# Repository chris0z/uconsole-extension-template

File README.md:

Licence | OSHWA
:-------------------------:|:-------------------------:
 | 
CERN-OHL-S-2.0

# uConsole Ext Template

This extension board is a basic Template for [uConsole](https://www.clockworkpi.com/uconsole).
Thanks to https://codeberg.org/argrento/uconsole-ext-usb-hub
## Schematic

## PCB

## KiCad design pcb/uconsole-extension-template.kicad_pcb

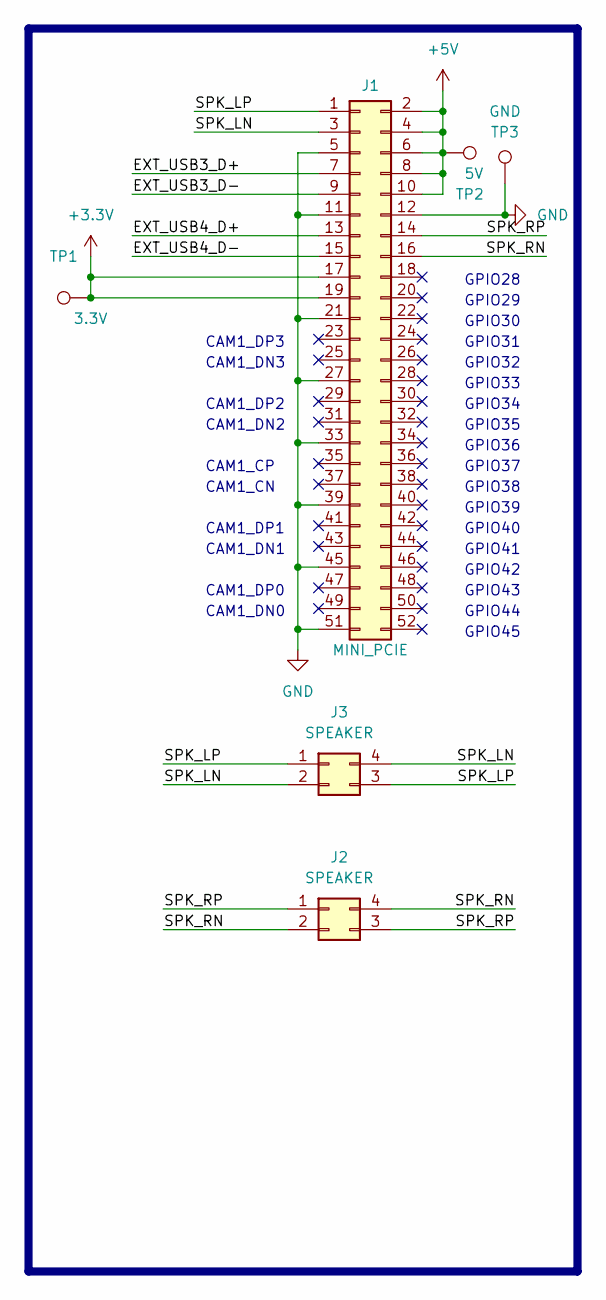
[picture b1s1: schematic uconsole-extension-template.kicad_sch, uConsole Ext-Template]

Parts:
J1: MINI_PCIE; mini_pcie_edge
J2, J3: SPEAKER; uConsole_speaker
TP1: 3.3V; PinHeader_1x01_P2.54mm_Vertical
TP2: 5V; PinHeader_1x01_P2.54mm_Vertical
TP3: GND; PinHeader_1x01_P2.54mm_Vertical

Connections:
+3.3V: J1.17, J1.19, TP1.1
+5V: J1.2, J1.4, J1.6, J1.8, J1.10, TP2.1
/EXT_USB3_D+: J1.7
/EXT_USB3_D-: J1.9
/EXT_USB4_D+: J1.13
/EXT_USB4_D-: J1.15
/SPK_LN: J1.3, J3.2, J3.4
/SPK_LP: J1.1, J3.1, J3.3
/SPK_RN: J1.16, J2.2, J2.4
/SPK_RP: J1.14, J2.1, J2.3
GND: J1.5, J1.11, J1.12, J1.21, J1.27, J1.33, J1.39, J1.45, J1.51, TP3.1

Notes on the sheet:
CAM1_DN1
GPIO43
CAM1_DP3
CAM1_DP0
GPIO31
GPIO42
CAM1_DN3
GPIO29
CAM1_DP2
GPIO41
CAM1_DP1
GPIO32
GPIO28
GPIO38
GPIO30
CAM1_DN2
CAM1_DN0
GPIO39
CAM1_CP
GPIO34
GPIO37
GPIO33
CAM1_CN
GPIO36
GPIO35
GPIO44
GPIO45
GPIO40

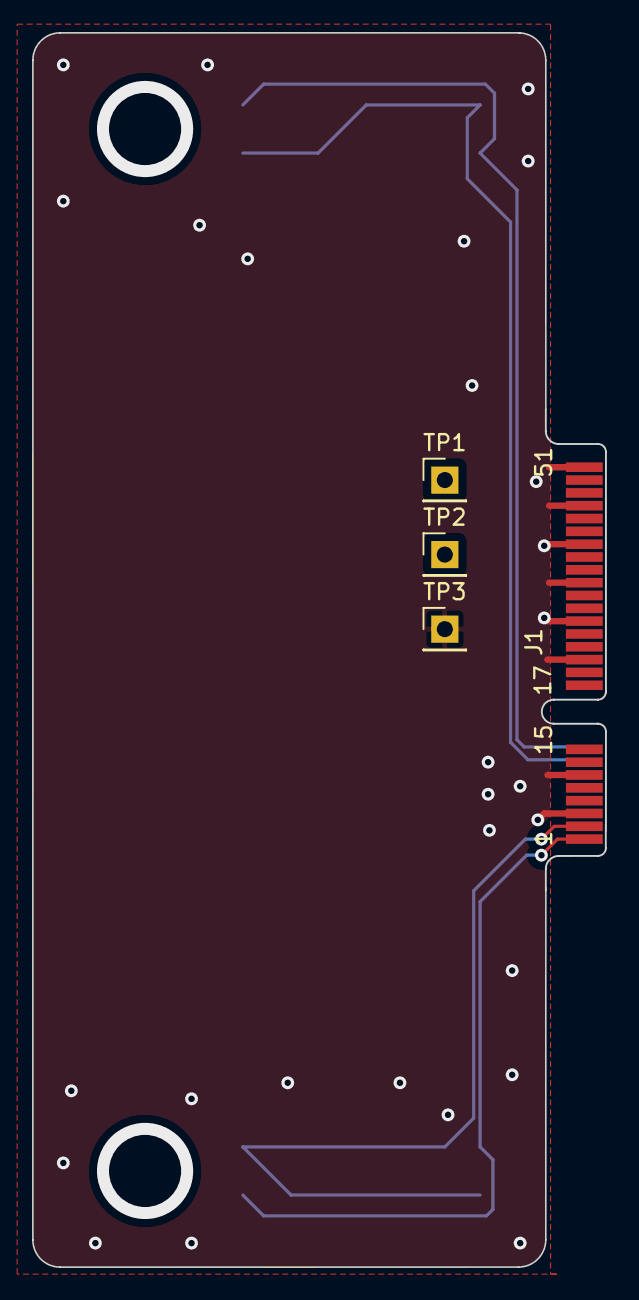
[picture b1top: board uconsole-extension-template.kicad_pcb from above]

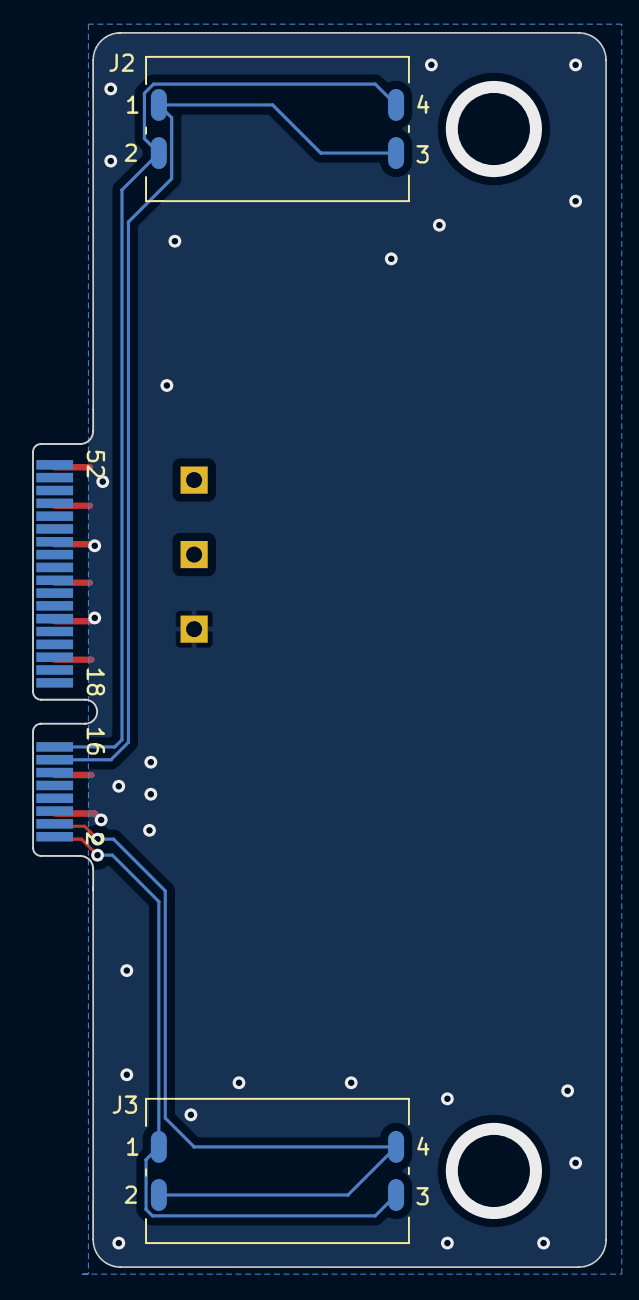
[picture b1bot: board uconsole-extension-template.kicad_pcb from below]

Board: 2 copper layers, 35.7 x 77.0 mm, 6 parts (2 on the bottom side), 7 nets.

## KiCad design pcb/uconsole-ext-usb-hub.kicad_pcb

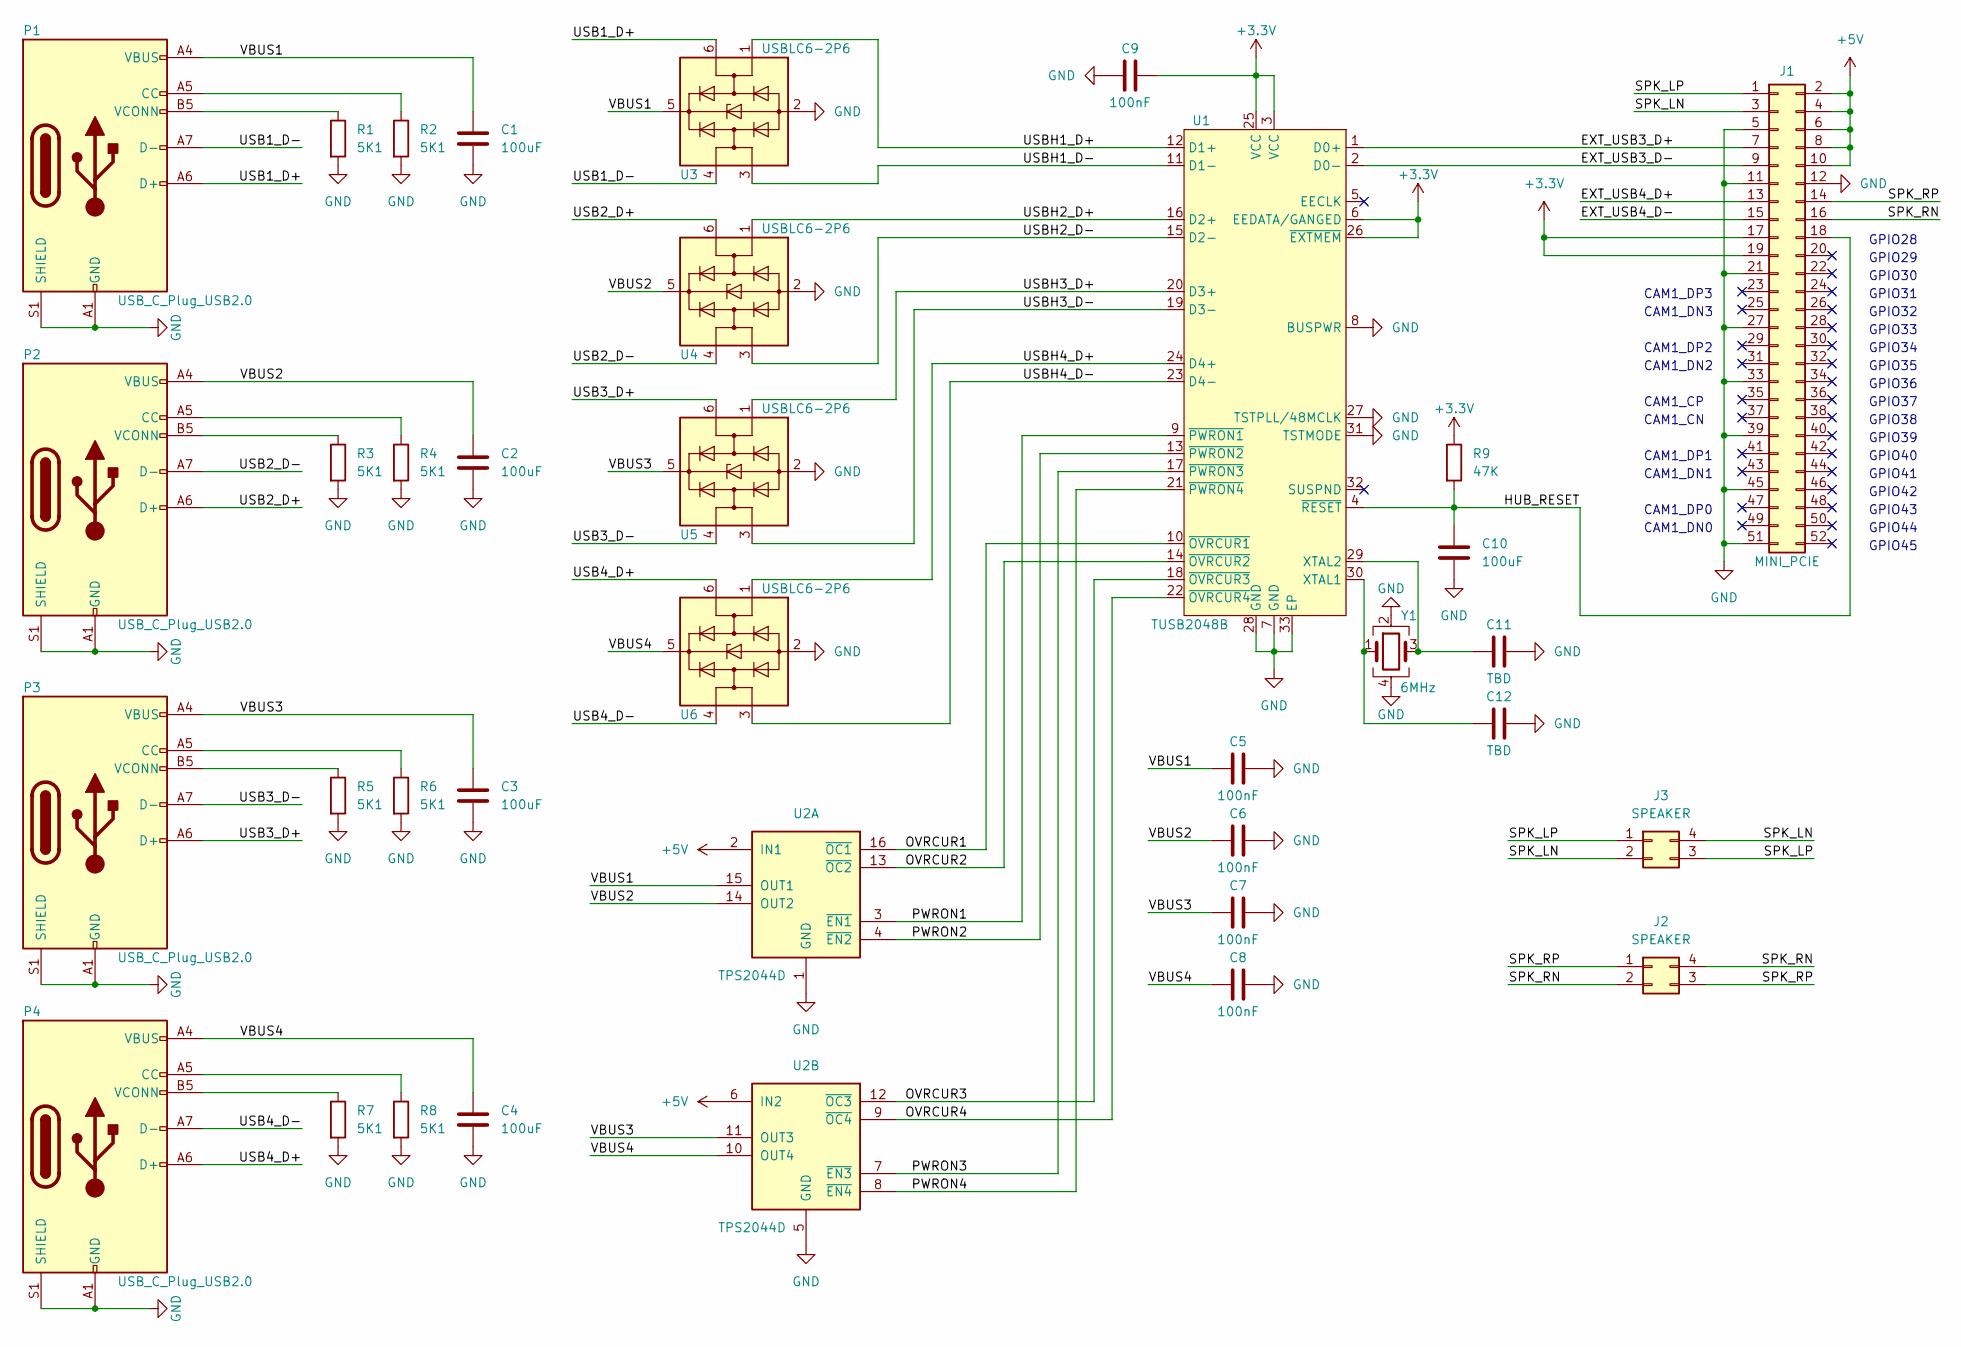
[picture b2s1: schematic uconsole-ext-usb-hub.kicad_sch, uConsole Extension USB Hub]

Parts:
C1, C2, C3, C4, C10: 100uF; C_0805_2012Metric
C5, C6, C7, C8, C9: 100nF; C_0603_1608Metric
C11, C12: TBD; C_0603_1608Metric
J1: MINI_PCIE; mini_pcie_edge
J2, J3: SPEAKER; uConsole_speaker
P1, P2, P3, P4: USB_C_Plug_USB2.0; USB_C_Receptacle_GCT_USB4105-xx-A_16P_TopMnt_Horizontal
R1, R2, R3, R4, R5, R6, R7, R8: 5K1; R_0603_1608Metric
R9: 47K; R_0603_1608Metric
U1: TUSB2048B; QFN-32-1EP_5x5mm_P0.5mm_EP3.3x3.3mm_ThermalVias
U2: TPS2044D; SOIC-16_3.9x9.9mm_P1.27mm
U3, U4, U5, U6: USBLC6-2P6; SOT-666
Y1: 6MHz; Crystal_SMD_2016-4Pin_2.0x1.6mm

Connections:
+3.3V: C9.1, J1.17, J1.19, R9.1, U1.3 (VCC), U1.6 (EEDATA/GANGED), U1.25 (VCC), U1.26 (~EXTMEM)
+5V: J1.2, J1.4, J1.6, J1.8, J1.10, U2.2 (IN1), U2.6 (IN2)
/EXT_USB3_D+: J1.7, U1.1 (D0+)
/EXT_USB3_D-: J1.9, U1.2 (D0-)
/EXT_USB4_D+: J1.13
/EXT_USB4_D-: J1.15
/HUB_RESET: C10.1, J1.18, R9.2, U1.4 (~RESET)
/OVRCUR1: U1.10 (~OVRCUR1), U2.16 (~OC1)
/OVRCUR2: U1.14 (~OVRCUR2), U2.13 (~OC2)
/OVRCUR3: U1.18 (~OVRCUR3), U2.12 (~OC3)
/OVRCUR4: U1.22 (~OVRCUR4), U2.9 (~OC4)
/PWRON1: U1.9 (~PWRON1), U2.3 (~EN1)
/PWRON2: U1.13 (~PWRON2), U2.4 (~EN2)
/PWRON3: U1.17 (~PWRON3), U2.7 (~EN3)
/PWRON4: U1.21 (~PWRON4), U2.8 (~EN4)
/SPK_LN: J1.3, J3.2, J3.4
/SPK_LP: J1.1, J3.1, J3.3
/SPK_RN: J1.16, J2.2, J2.4
/SPK_RP: J1.14, J2.1, J2.3
/USB1_D+: P1.A6 (D+), U3.6 (I/O1)
/USB1_D-: P1.A7 (D-), U3.4 (I/O2)
/USB2_D+: P2.A6 (D+), U4.6 (I/O1)
/USB2_D-: P2.A7 (D-), U4.4 (I/O2)
/USB3_D+: P3.A6 (D+), U5.6 (I/O1)
/USB3_D-: P3.A7 (D-), U5.4 (I/O2)
/USB4_D+: P4.A6 (D+), U6.6 (I/O1)
/USB4_D-: P4.A7 (D-), U6.4 (I/O2)
/USBH1_D+: U1.12 (D1+), U3.1 (I/O1)
/USBH1_D-: U1.11 (D1-), U3.3 (I/O2)
/USBH2_D+: U1.16 (D2+), U4.1 (I/O1)
/USBH2_D-: U1.15 (D2-), U4.3 (I/O2)
/USBH3_D+: U1.20 (D3+), U5.1 (I/O1)
/USBH3_D-: U1.19 (D3-), U5.3 (I/O2)
/USBH4_D+: U1.24 (D4+), U6.1 (I/O1)
/USBH4_D-: U1.23 (D4-), U6.3 (I/O2)
/VBUS1: C1.1, C5.1, P1.A4 (VBUS), P1.A9 (VBUS), P1.B4 (VBUS), P1.B9 (VBUS), U2.15 (OUT1), U3.5 (VBUS)
/VBUS2: C2.1, C6.1, P2.A4 (VBUS), P2.A9 (VBUS), P2.B4 (VBUS), P2.B9 (VBUS), U2.14 (OUT2), U4.5 (VBUS)
/VBUS3: C3.1, C7.1, P3.A4 (VBUS), P3.A9 (VBUS), P3.B4 (VBUS), P3.B9 (VBUS), U2.11 (OUT3), U5.5 (VBUS)
/VBUS4: C4.1, C8.1, P4.A4 (VBUS), P4.A9 (VBUS), P4.B4 (VBUS), P4.B9 (VBUS), U2.10 (OUT4), U6.5 (VBUS)
GND: C1.2, C2.2, C3.2, C4.2, C5.2, C6.2, C7.2, C8.2, C9.2, C10.2, C11.2, C12.2, J1.5, J1.11, J1.12, J1.21, J1.27, J1.33, J1.39, J1.45, J1.51, P1.A1 (GND), P1.A12 (GND), P1.B1 (GND), P1.B12 (GND), P1.S1 (SHIELD), P2.A1 (GND), P2.A12 (GND), P2.B1 (GND), P2.B12 (GND), P2.S1 (SHIELD), P3.A1 (GND), P3.A12 (GND), P3.B1 (GND), P3.B12 (GND), P3.S1 (SHIELD), P4.A1 (GND), P4.A12 (GND), P4.B1 (GND), P4.B12 (GND), P4.S1 (SHIELD), R1.2, R2.2, R3.2, R4.2, R5.2, R6.2, R7.2, R8.2, U1.7 (GND), U1.8 (BUSPWR), U1.27 (TSTPLL/48MCLK), U1.28 (GND), U1.31 (TSTMODE), U1.33 (EP), U2.1 (GND), U2.5 (GND), U3.2 (GND), U4.2 (GND), U5.2 (GND), U6.2 (GND), Y1.2, Y1.4
unnamed: P1.A5 (CC), R2.1
unnamed: P1.B5 (VCONN), R1.1
unnamed: P2.A5 (CC), R4.1
unnamed: P2.B5 (VCONN), R3.1
unnamed: P3.A5 (CC), R6.1
unnamed: P3.B5 (VCONN), R5.1
unnamed: P4.A5 (CC), R8.1
unnamed: P4.B5 (VCONN), R7.1
unnamed: C12.1, U1.30 (XTAL1), Y1.1
unnamed: C11.1, U1.29 (XTAL2), Y1.3

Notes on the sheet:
CAM1_DN1
GPIO43
CAM1_DP3
CAM1_DP0
GPIO31
GPIO42
CAM1_DN3
GPIO29
CAM1_DP2
GPIO41
CAM1_DP1
GPIO32
GPIO28
GPIO38
GPIO30
CAM1_DN2
CAM1_DN0
GPIO39
CAM1_CP
GPIO34
GPIO37
GPIO33
CAM1_CN
GPIO36
GPIO35
GPIO44
GPIO45
GPIO40

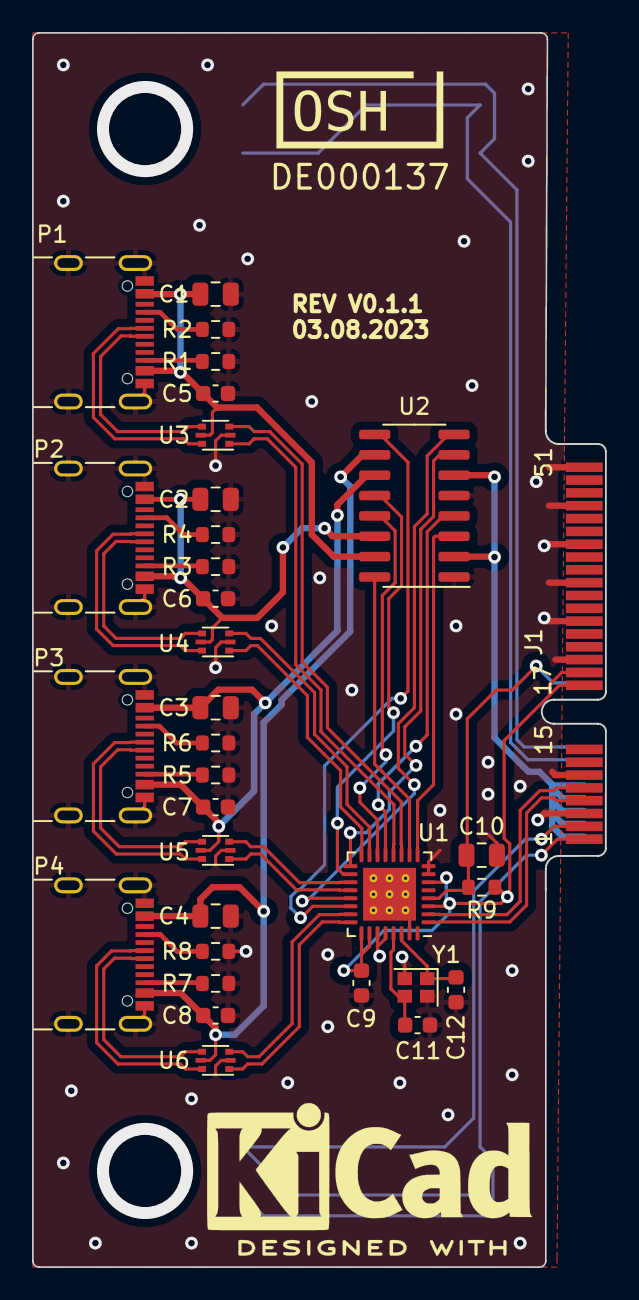
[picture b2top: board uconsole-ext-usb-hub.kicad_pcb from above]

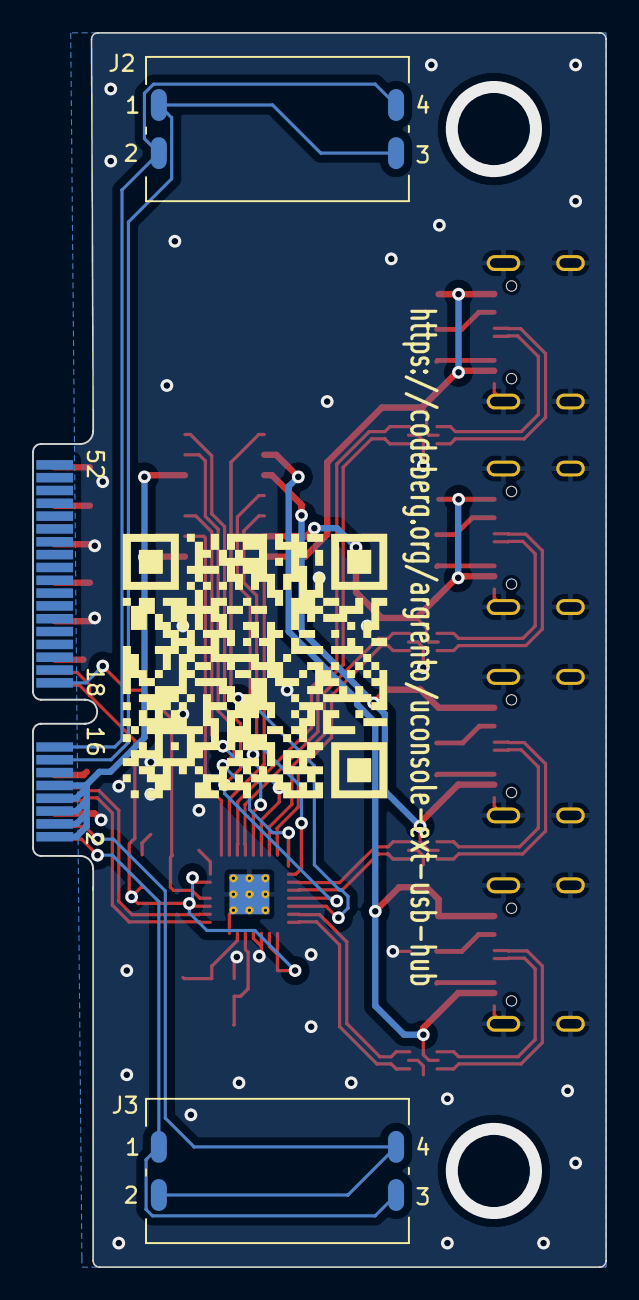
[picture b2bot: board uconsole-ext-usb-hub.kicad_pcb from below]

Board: 2 copper layers, 35.7 x 77.0 mm, 37 parts (3 on the bottom side), 48 nets.

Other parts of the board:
OSHW_Dual_0.25_Scale: DE000137; OSHW_Dual_0.25_Scale
QR: qr-https--codeberg.org-argrento-uconsole-ext-usb-hub

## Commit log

2023-07-23 sch: add speakers
2023-07-26 First PCB version
    * Added speakers
    * Initial pcb
2023-08-03 Update version to 0.1.1
    * Add OSHWA certification mark
    * Add license info
2023-08-09 Init-Commit
